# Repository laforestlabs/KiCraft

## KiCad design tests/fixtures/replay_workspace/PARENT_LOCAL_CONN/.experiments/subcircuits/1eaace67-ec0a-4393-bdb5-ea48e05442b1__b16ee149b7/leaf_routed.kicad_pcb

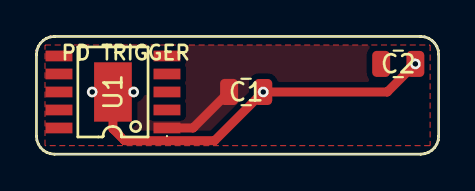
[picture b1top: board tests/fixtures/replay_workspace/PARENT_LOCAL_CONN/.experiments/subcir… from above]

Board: 2 copper layers, 22.3 x 6.5 mm, 3 parts (0 on the bottom side), 2 nets.

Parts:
C1: 1uF; C_0805_2012Metric
C2: 10uF; C_0805_2012Metric
U1: CH224K; ESSOP-10_L4.9-W3.9-P1.0-LS6.0-TL-EP

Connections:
+3V3: C1.1, U1.1
GND: C1.2, C2.2, U1.11

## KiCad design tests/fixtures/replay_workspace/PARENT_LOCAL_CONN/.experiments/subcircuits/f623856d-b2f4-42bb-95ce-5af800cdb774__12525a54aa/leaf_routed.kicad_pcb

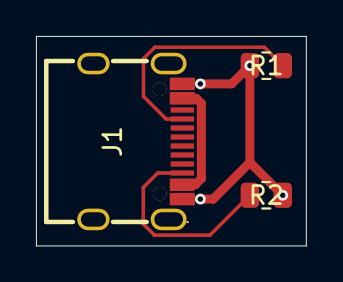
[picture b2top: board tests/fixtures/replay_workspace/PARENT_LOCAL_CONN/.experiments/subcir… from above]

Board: 2 copper layers, 15.0 x 11.6 mm, 3 parts (0 on the bottom side), 4 nets.

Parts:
J1: USB-C Receptacle; USB-C_SMD-TYPE-C-31-M-12_1
R1, R2: 5.1k; R_0805_2012Metric

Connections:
CC1: J1.A5, R1.1
CC2: J1.B5, R2.1
GND: J1.A1B12, J1.B1A12, R1.2, R2.2
VBUS_IN: J1.A4B9, J1.B4A9

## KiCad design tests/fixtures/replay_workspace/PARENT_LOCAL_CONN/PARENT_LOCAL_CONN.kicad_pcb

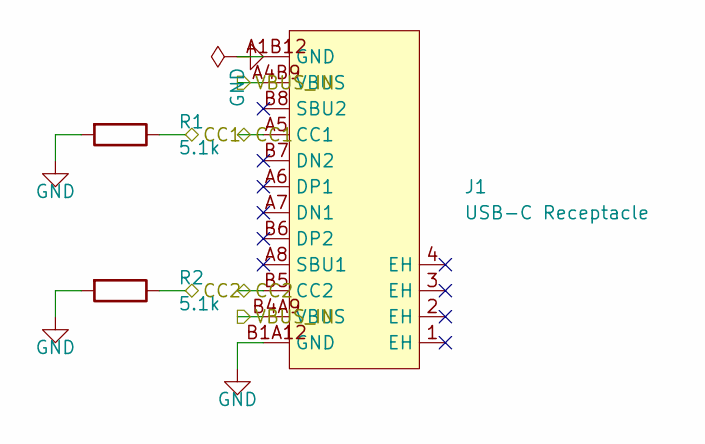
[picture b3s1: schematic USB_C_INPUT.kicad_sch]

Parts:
J1: USB-C Receptacle; USB-C_SMD-TYPE-C-31-M-12_1
R1, R2: 5.1k; R_0805_2012Metric

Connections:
CC1: J1.A5 (CC1), R1.1; also elsewhere on the board
CC2: J1.B5 (CC2), R2.1; also elsewhere on the board
GND: J1.A1B12 (GND), J1.B1A12 (GND), R1.2, R2.2; also elsewhere on the board
VBUS_IN: J1.A4B9 (VBUS), J1.B4A9 (VBUS); also elsewhere on the board

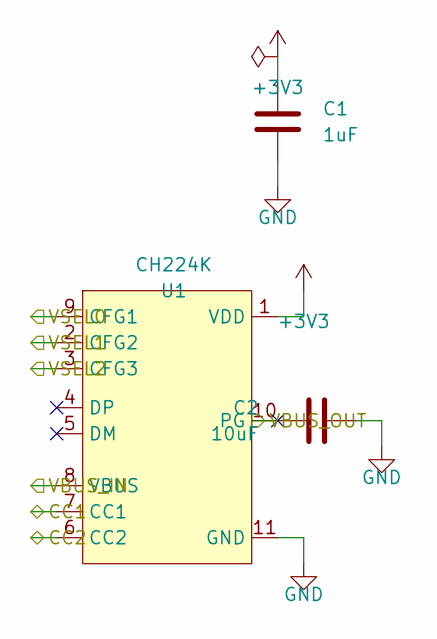
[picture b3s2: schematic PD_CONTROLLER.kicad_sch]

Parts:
C1: 1uF; C_0805_2012Metric
C2: 10uF; C_0805_2012Metric
U1: CH224K; ESSOP-10_L4.9-W3.9-P1.0-LS6.0-TL-EP

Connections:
+3V3: C1.1, U1.1 (VDD); also elsewhere on the board
CC1: U1.7 (CC1); also elsewhere on the board
CC2: U1.6 (CC2); also elsewhere on the board
GND: C1.2, C2.2, U1.11 (GND); also elsewhere on the board
VBUS_IN: U1.8 (VBUS); also elsewhere on the board
VBUS_OUT: C2.1, U1.10 (PG); also elsewhere on the board
VSEL0: U1.9 (CFG1); also elsewhere on the board
VSEL1: U1.2 (CFG2); also elsewhere on the board
VSEL2: U1.3 (CFG3); also elsewhere on the board

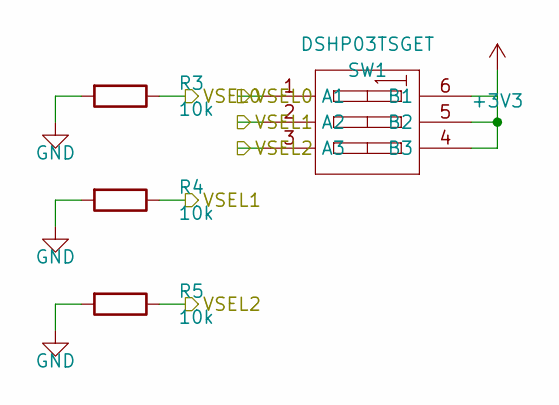
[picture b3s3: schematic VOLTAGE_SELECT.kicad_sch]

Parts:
R3, R4, R5: 10k; R_0805_2012Metric
SW1: DSHP03TSGET; SW-SMD_6P-L5.4-W5.4-P1.27-LS8.4

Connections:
+3V3: SW1.4 (B3), SW1.5 (B2), SW1.6 (B1); also elsewhere on the board
GND: R3.2, R4.2, R5.2; also elsewhere on the board
VSEL0: R3.1, SW1.1 (A1); also elsewhere on the board
VSEL1: R4.1, SW1.2 (A2); also elsewhere on the board
VSEL2: R5.1, SW1.3 (A3); also elsewhere on the board

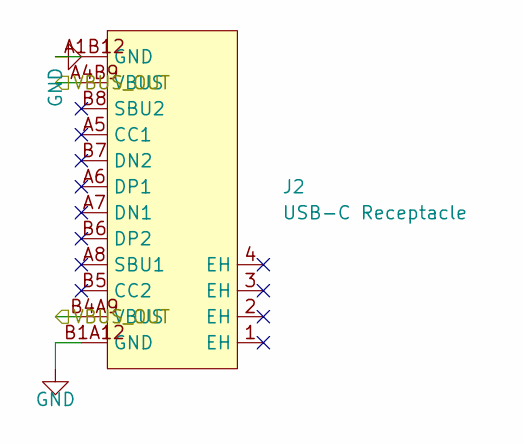
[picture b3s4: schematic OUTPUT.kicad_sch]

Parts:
J2: USB-C Receptacle; USB-C_SMD-TYPE-C-31-M-12_1

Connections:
GND: J2.A1B12 (GND), J2.B1A12 (GND); also elsewhere on the board
VBUS_OUT: J2.A4B9 (VBUS), J2.B4A9 (VBUS); also elsewhere on the board

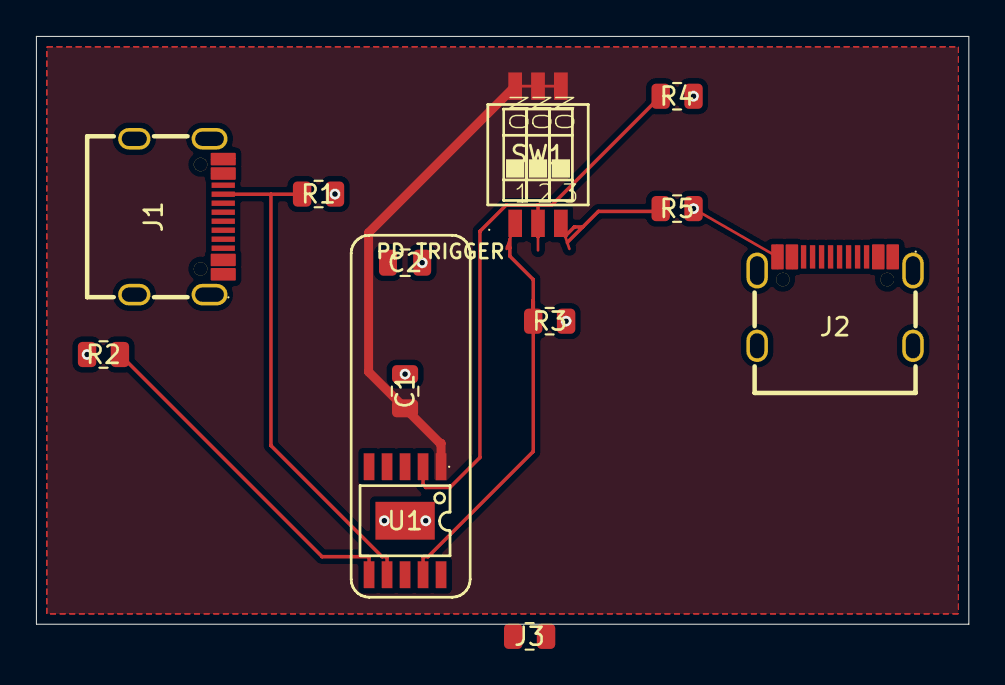
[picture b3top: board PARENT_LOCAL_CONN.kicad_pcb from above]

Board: 2 copper layers, 51.8 x 32.7 mm, 12 parts (0 on the bottom side), 9 nets.

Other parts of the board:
J3: 10k; R_0805_2012Metric

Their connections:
GND: J3.1, J3.2; also elsewhere on the board

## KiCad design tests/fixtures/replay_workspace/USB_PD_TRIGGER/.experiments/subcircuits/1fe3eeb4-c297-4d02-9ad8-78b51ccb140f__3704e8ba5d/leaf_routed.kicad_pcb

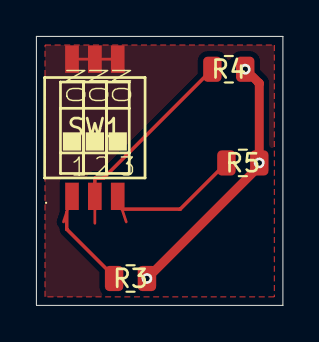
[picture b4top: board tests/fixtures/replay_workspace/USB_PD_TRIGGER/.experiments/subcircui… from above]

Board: 2 copper layers, 13.7 x 14.9 mm, 4 parts (0 on the bottom side), 5 nets.

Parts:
R3, R4, R5: 10k; R_0805_2012Metric
SW1: DSHP03TSGET; SW-SMD_6P-L5.4-W5.4-P1.27-LS8.4

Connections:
+3V3: SW1.4, SW1.5, SW1.6
GND: R3.2, R4.2, R5.2
VSEL0: R3.1, SW1.1
VSEL1: R4.1, SW1.2
VSEL2: R5.1, SW1.3

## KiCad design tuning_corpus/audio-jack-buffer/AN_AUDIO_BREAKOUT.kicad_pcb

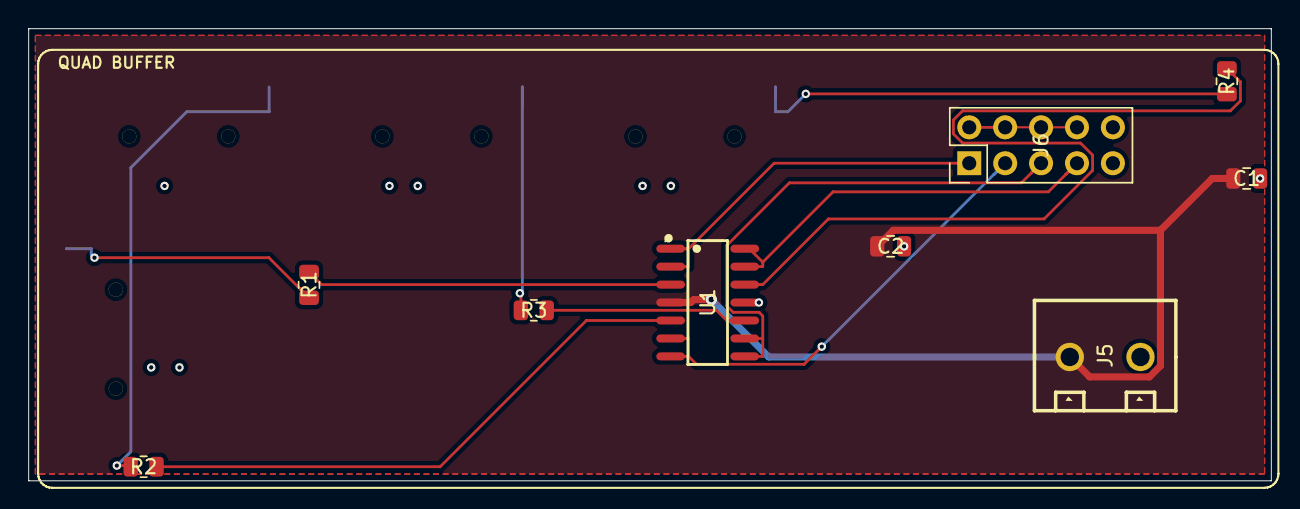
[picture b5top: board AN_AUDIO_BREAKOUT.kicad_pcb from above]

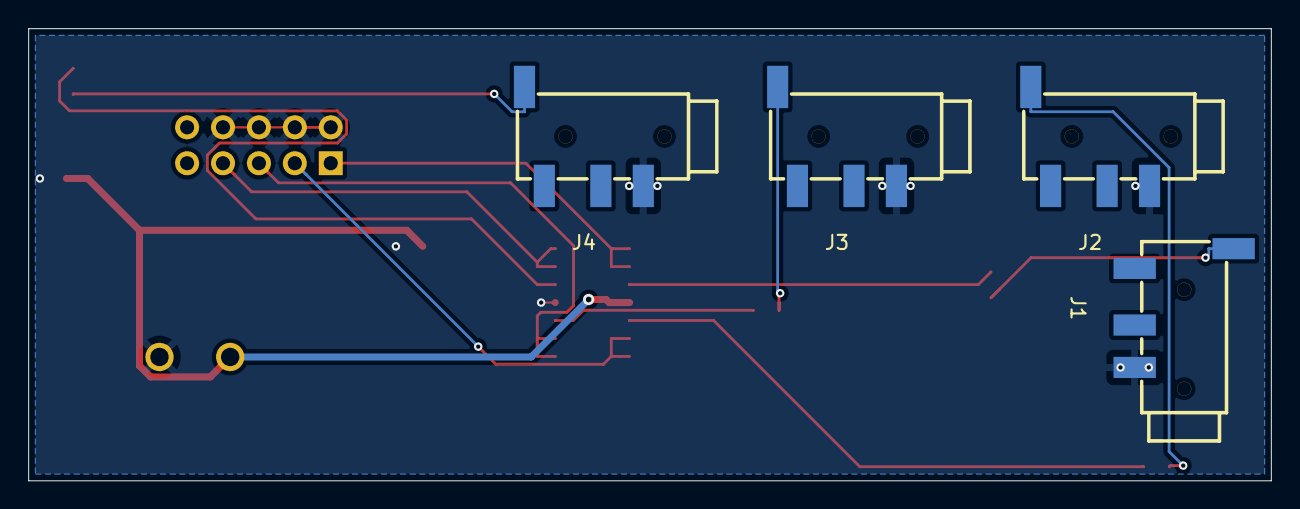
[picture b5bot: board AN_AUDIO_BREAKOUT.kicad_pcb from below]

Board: 2 copper layers, 87.9 x 32.0 mm, 13 parts (4 on the bottom side), 14 nets.

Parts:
C1: 10ÂµF; C_0805_2012Metric
C2: 0.1ÂµF; C_0805_2012Metric
J1, J2, J3, J4: 3.5mm TS Jack; AUDIO-SMD_PJ-320D-1
J5: Screw Terminal 2P; CONN-TH_WJ126V-5.0-2P
J6: Pin Header 2x05; PinHeader_2x05_P2.54mm_Vertical
R1, R2, R3, R4: 1k; R_0805_2012Metric
U1: MCP6004; SOIC-14_L8.7-W3.9-P1.27-LS6.0-BL

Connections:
+5V: C1.1, C2.1, J5.1, U1.4
CH1_IN: J1.1, R1.1
CH1_OUT: J6.1, U1.1, U1.2
CH1_POS: R1.2, U1.3
CH2_IN: J2.1, R2.1
CH2_OUT: J6.3, U1.6, U1.7
CH2_POS: R2.2, U1.5
CH3_IN: J3.1, R3.1
CH3_OUT: J6.5, U1.8, U1.9
CH3_POS: R3.2, U1.10
CH4_IN: J4.1, R4.1
CH4_OUT: J6.7, U1.13, U1.14
CH4_POS: R4.2, U1.12
GND: C1.2, C2.2, J1.2, J2.2, J3.2, J4.2, J5.2, J6.2, J6.4, J6.6, J6.8, U1.11

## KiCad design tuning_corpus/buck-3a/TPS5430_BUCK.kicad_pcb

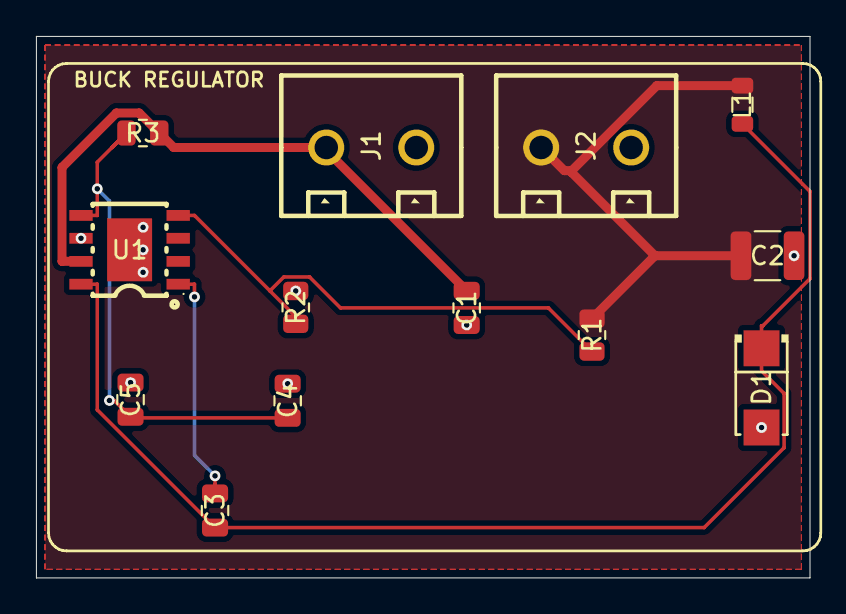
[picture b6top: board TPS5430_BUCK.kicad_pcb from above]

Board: 2 copper layers, 43.0 x 30.1 mm, 13 parts (0 on the bottom side), 7 nets.

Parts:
C1: 10ÂµF; C_0805_2012Metric
C2: 47ÂµF; C_1210_3225Metric
C3, C4: 0.01ÂµF; C_0805_2012Metric
C5: 3300pF; C_0805_2012Metric
D1: SS34; SMA_L4.3-W2.6-LS5.2-RD
J1, J2: 2-pin 5mm screw terminal; CONN-TH_WJ126V-5.0-2P
L1: 10ÂµH; L_0805_2012Metric
R1: 16.2k; R_0805_2012Metric
R2: 9.53k; R_0805_2012Metric
R3: 10k; R_0805_2012Metric
U1: TPS5430DDAR; ESOP-8_L4.9-W3.9-P1.27-LS6.0-TL-EP

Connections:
+3V3: C2.1, J2.1, L1.2, R1.1
+5V: C1.1, J1.1, R3.1, U1.7
BOOT: C3.1, U1.1
ENABLE: C4.1, C5.1, R3.2, U1.5
FB: R1.2, R2.1, U1.4
GND: C1.2, C2.2, C4.2, C5.2, D1.2, J1.2, J2.2, R2.2, U1.6, U1.9
SW: C3.2, D1.1, L1.1, U1.8
